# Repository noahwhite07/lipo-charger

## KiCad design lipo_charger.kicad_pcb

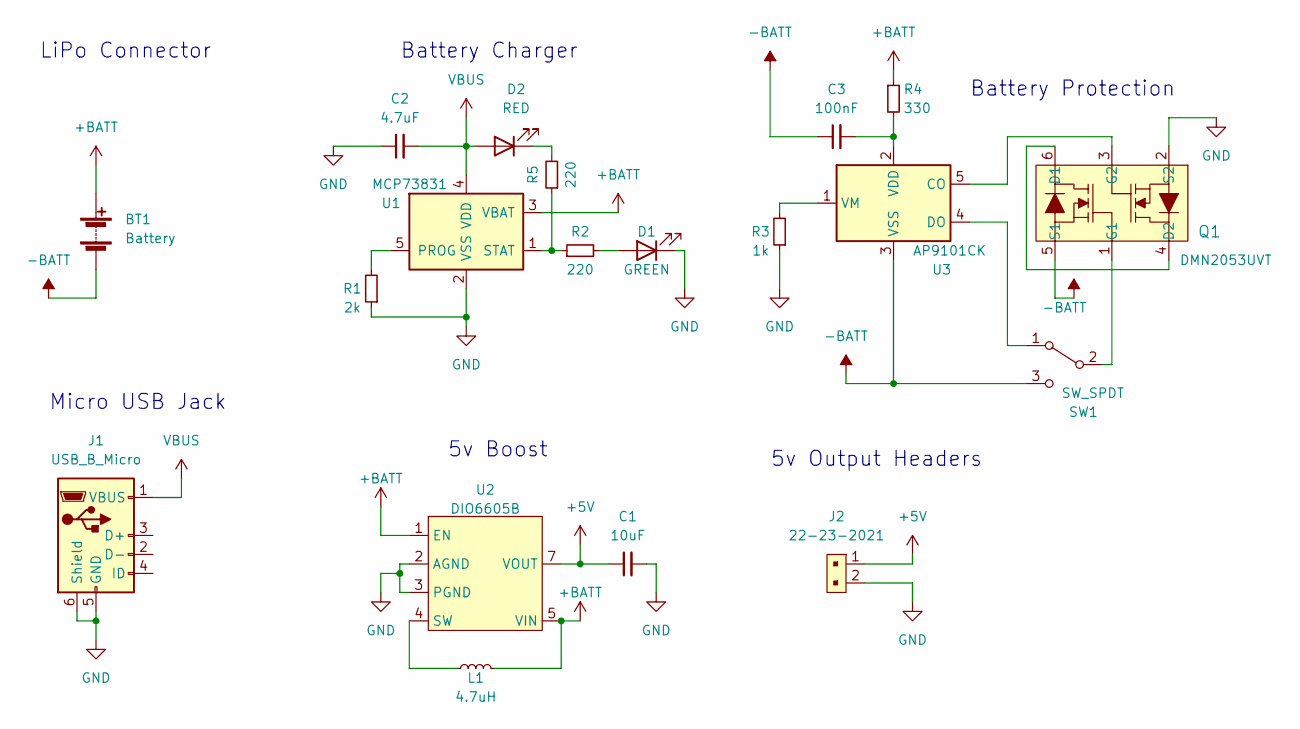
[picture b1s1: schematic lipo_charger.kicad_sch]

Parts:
BT1: Battery; JST_PH_B2B-PH-SM4-TB_1x02-1MP_P2.00mm_Vertical
C1: 10uF; C_0805_2012Metric
C2: 4.7uF; C_0805_2012Metric
C3: 100nF; C_0805_2012Metric
D1: GREEN; LED_0805_2012Metric
D2: RED; LED_0805_2012Metric
J1: USB_B_Micro; USB_Micro-B_GCT_USB3076-30-A
J2: 22-23-2021; PinHeader_1x02_P2.54mm_Vertical; MPN 22-23-2021; Digi-Key_PN WM4200-ND
L1: 4.7uH; L_0805_2012Metric
Q1: DMN2053UVT; TSOT-23-6
R1: 2k; R_0805_2012Metric_Pad1.20x1.40mm_HandSolder
R2, R5: 220; R_0805_2012Metric_Pad1.20x1.40mm_HandSolder
R3: 1k; R_0805_2012Metric_Pad1.20x1.40mm_HandSolder
R4: 330; R_0805_2012Metric_Pad1.20x1.40mm_HandSolder
SW1: SW_SPDT; SW_CuK_OS102011MA1QN1_SPDT_Angled
U1: MCP73831; SOT-23-5
U2: DIO6605B; DFN-8-1EP_3x2mm_P0.5mm_EP1.6x1.5mm
U3: AP9101CK; SOT-23-5

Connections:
+5V: C1.1, J2.1, U2.7 (VOUT)
+BATT: BT1.1 (+), L1.2, R4.1, U1.3 (VBAT), U2.1 (EN), U2.5 (VIN)
-BATT: BT1.2 (-), C3.1, Q1.5 (S1), SW1.3 (C), U3.3 (VSS)
GND: C1.2, C2.1, D1.1 (K), J1.5 (GND), J1.6 (Shield), J2.2, Q1.2 (S2), R1.1, R3.1, U1.2 (VSS), U2.2 (AGND), U2.3 (PGND), U2.9
unnamed: C3.2, R4.2, U3.2 (VDD)
unnamed: D1.2 (A), R2.2
unnamed: D2.1 (K), R5.2
unnamed: L1.1, U2.4 (SW)
unnamed: Q1.1 (G1), SW1.2 (B)
unnamed: Q1.3 (G2), U3.5 (CO)
unnamed: Q1.4 (D2), Q1.6 (D1)
unnamed: R1.2, U1.5 (PROG)
unnamed: R2.1, R5.1, U1.1 (STAT)
unnamed: R3.2, U3.1 (VM)
unnamed: SW1.1 (A), U3.4 (DO)
VBUS: C2.2, D2.2 (A), J1.1 (VBUS), U1.4 (VDD)

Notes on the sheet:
Battery Charger
5v Boost
Battery Protection
5v Output Headers
LiPo Connector
Micro USB Jack

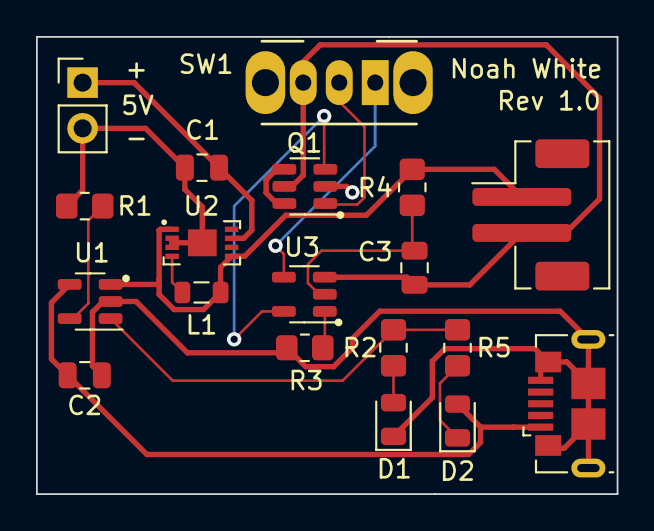
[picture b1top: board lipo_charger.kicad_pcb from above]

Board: 2 copper layers, 32.3 x 25.4 mm, 19 parts (0 on the bottom side), 16 nets.

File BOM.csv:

Source:,D:\Program Files\KiCad_6\projects\lipo_charger\lipo_charger.kicad_sch,,,,,,,
Date:,2/9/2023 15:37,,,,,,,
Tool:,Eeschema (6.0.10),,,,,,,
Generator:,D:\Program Files\KiCad_6\bin\scripting\plugins/bom_csv_grouped_by_value.py,,,,,,,
Component Count:,19,,,,,,,
,,,,,,,,
,,,,,,,,
,,,,,,,,
,,,,,,,,
Collated Components:,,,,,,,,
,,,,,,,,
Item,Qty,Reference(s),Value,Link,Datasheet,Description,MPN,Price
1,1,BT1,Battery,,~,LiPo Connector,,
2,1,C1,10uF,https://www.mouser.com/ProductDetail/Samsung-Electro-Mechani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,~,Capacitor,CL21A106KOQNNNE,0.1
3,1,C2,4.7uF,https://www.mouser.com/ProductDetail/Samsung-Electro-Mechani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,~,Capacitor,CL21A475KPFNNNE,0.1
4,1,C3,100nF,https://www.mouser.com/ProductDetail/Samsung-Electro-Mechani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,~,Capacitor,CL21F104ZBANNNC,0.1
5,1,D1,GREEN,https://www.mouser.com/ProductDetail/Wurth-Elektronik/150080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,~,Green LED,150080VS75000,0.19
6,1,D2,RED,https://www.mouser.com/ProductDetail/Wurth-Elektronik/150080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,~,Red LED,150080RS75000,0.19
7,1,J1,USB_B_Micro,https://www.mouser.com/ProductDetail/GCT/USB3076-30-A?qs=KUo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,~,Micro USB Jack,USB3076-30-A,0.7
8,1,J2,~,~,,Pin Headers,~,0
9,1,L1,4.7uH,https://www.mouser.com/ProductDetail/Murata-Electronics/LQM2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,~,Inductor,LQM21PN4R7MGRD,0.23
10,1,Q1,DMN2053UVT-7,https://www.mouser.com/ProductDetail/Diodes-Incorporated/DMN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,https://www.diodes.com/assets/Datasheets/ds30120.pdf,Dual NMOS,DMN2053UVT-7,0.37
11,1,R1,2k,https://www.mouser.com/ProductDetail/YAGEO/AC0805FR-072KL?qs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,~,Resistor,AC0805FR-072KL,0.1
12,2,"R2, R5",220,https://www.mouser.com/ProductDetail/YAGEO/RC0805FR-07220RL?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,~,Resistor,RC0805FR-07220RL,0.1
13,1,R3,1k,https://www.mouser.com/ProductDetail/YAGEO/RC0805JR-071K1L?q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,~,Resistor,RC0805JR-071K1L,0.1
14,1,R4,330,https://www.mouser.com/ProductDetail/YAGEO/RC0805FR-07332RL?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,~,Resistor,RC0805FR-07332RL,0.1
15,1,SW1,SW_SPDT,https://www.mouser.com/ProductDetail/CK/OS102011MA1QN1?qs=Wt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,~,SPDT Switch,OS102011MA1QN1,0.5
16,1,U1,MCP73831,https://www.mouser.com/ProductDetail/Microchip-Technology/MC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,http://ww1.microchip.com/downloads/en/DeviceDoc/20001984g.pdf,Charging IC,MCP73831T-2DCI/OT,0.77
17,1,U2,DIO6605B,https://www.mouser.com/ProductDetail/DIOO-Microcircuits/DIO6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,h,Boost IC,DIO6605BFN8,0.6
18,1,U3,AP9101CK,https://www.mouser.com/ProductDetail/Diodes-Incorporated/AP9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,https://www.diodes.com/assets/Datasheets/AP9101C.pdf,Protection IC,AP9101CK6-AYTRG1,0.46
,,,,,,,,
,,,,,,,,
,,,,,,,Total,4.81
,,,,,,,,
,,,,,,,,
,,,,,,,,
CL21A106KOQNNNE,1,,,,,,,
CL21A475KPFNNNE,1,,,,,,,
CL21F104ZBANNNC,1,,,,,,,
150080VS75000,1,,,,,,,
150080RS75000,1,,,,,,,
USB3076-30-A,1,,,,,,,
LQM21PN4R7MGRD,1,,,,,,,
DMN2053UVT-7,1,,,,,,,
AC0805FR-072KL,1,,,,,,,
RC0805FR-07220RL,2,,,,,,,
RC0805JR-071K1L,1,,,,,,,
RC0805FR-07332RL,1,,,,,,,
OS102011MA1QN1,1,,,,,,,
MCP73831T-2DCI/OT,1,,,,,,,
DIO6605BFN8,1,,,,,,,
AP9101CK6-AYTRG1,1,,,,,,,

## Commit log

2023-01-30 Finish first schematic draft
2023-01-31 Add remaining passive components
2023-02-04 Place and route components
2023-02-04 Finish routing and generate gerbers
2023-02-05 Modify schematic symbols
2023-02-05 Add lipo connector footprint
2023-02-05 Add datasheets directory
2023-02-05 Create footprint for boost IC and reroute
2023-02-06 Fix incorrect value for R3
2023-02-06 Add datasheet for MOSFET IC
2023-02-08 Fix misplaced capacitor
2023-02-10 Generate BOM
2023-02-11 Replace Q1 NMOS and fix R3 val
2023-02-11 Reroute PCB with new Q2 footprint
2023-02-14 Replace switch and reroute
2023-02-14 Finish BOM
2023-02-14 Replace switch and rewire schematic
2023-02-14 Replace switch footprint on PCB
2023-02-15 Completely reroute PCB
2023-02-15 Re-generate gerbers
